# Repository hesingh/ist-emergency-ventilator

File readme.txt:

ABOUT:
The enclosed files belong to the eVent IST ventilator project, inspired by the MIT E-Vent project (see https://e-vent.mit.edu/). We developed the ventilator system using technical documentation of MIT, infrastructure of IST AUSTIRA and consulting of three medical practitioners. We developed and built with great care and focus on stability and safety, still the device is not certified and not built according to all applicable regulations. Please note that this is work in progress and has never been tested on a human. The goal of the eVent IST ventilator project is to provide a simple and fast to replicate system for emergency response, and was created in reaction to the COVID-19 crisis early 2020. Furthermore, its intention is not to replace common ventilator systems, but to bridge a situation where not enough conventional machines are available.

ATTRIBUTION:
Please notice that the eVent IST ventilator was developed using the information shared by the Massachusetts Institute of Technology (MIT). You can find information on the original MIT E-Vent project under https://e-vent.mit.edu/. All Terms of Use, found here: https://e-vent.mit.edu/terms-and-conditions/, concerning the original MIT content do apply.
3rd party libraries used: Encoder by Paul Stoffregen (https://github.com/PaulStoffregen/Encoder), LiquidCrystal (https://github.com/arduino-libraries/LiquidCrystal).

FOLDERS:

	Folder name	Description							Origin
	------------------------------------------------------------------------------------------------
	Electronics	contains files for the electronic parts of the ventilator	mostly MIT E-Vent
	License		contains relevant license files					https://opensource.org
	Mechanical	contains files for the mechanical parts of the ventilator	mostly MIT E-Vent
	Pictures	contains pictures of the machine				IST AUSTRIA
	Software	contains files for the software of the ventilator		IST AUSTRIA

COPYRIGHT AND LICENSE: 
Selected Content may be downloaded by you pursuant to these Terms of Use. All copyright in and to the original MIT E-Vent Design Specifications belong to MIT. MIT is making the Design Specifications freely available to you to use, subject to these Terms of Use and your agreement to give full attribution to MIT should you reproduce, display, disseminate, or distribute the Design Specifications. All copyright in and to content going beyond the MIT E-Vent Design Specifications, and especially the software, belong to IST AUSTRIA. If and to the extent you provide any feedback, suggestions, recommendations, analysis or other information or data to IST in connection with your use of the Content (“Feedback”), you hereby permit IST to use, reproduce, disclose, distribute, modify, and prepare derivative works of such Feedback for any purpose whatsoever in perpetuity. Any downloadable software is subject to the MIT Open Source license, found here: https://opensource.org/licenses/MIT.
3rd party libraries included: Encoder: (MIT License), LiquidCrystal: LGPL License v3 (https://opensource.org/licenses/LGPL-3.0).

DISCLAIMER OF WARRANTIES
YOU ACKNOWLEDGE THAT THE CONTENT IS IN RESEARCH PHASE AND ALL OUTCOMES FROM USE OF THE CONTENT ARE NOT KNOWN. YOUR USE OF THE CONTENT, INCLUDING THE DESIGN SPECIFICATIONS AND THE SOFTWARE, IS AT YOUR OWN RISK. THE CONTENT, INCLUDING THE DESIGN SPECIFICATIONS AND THE SOFTWARE, ARE PROVIDED ON AN “AS IS” AND “AS AVAILABLE” BASIS. 
IST AUSTRIA, ON BEHALF OF ITSELF AND ITS COLLABORATORS, MAKES NO REPRESENTATIONS, WARRANTIES OR COVENANTS, WHETHER STATUTORY, EXPRESS, IMPLIED, BY COURSE OF COMMUNICATION OR DEALING, OR OTHERWISE WITH RESPECT TO THE CONTENT, INCLUDING THE DESIGN SPECIFICATIONS AND THE SOFTWARE, AND ANY RESULTING DEVICE.  IST AUSTRIA, ON BEHALF OF ITSELF AND ITS COLLABORATORS, SPECIFICALLY DISCLAIMS ANY WARRANTY WITH REGARD TO FITNESS FOR ANY PARTICULAR PURPOSE, MERCHANTABILITY OR NON-INFRINGEMENT.
WITHOUT LIMITING THE GENERALITY OF THE FOREGOING, IST AUSTRIA, ON BEHALF OF ITSELF AND ITS COLLABORATORS, MAKES NO WARRANTY OF ANY KIND THAT THE CONTENT, INCLUDING THE DESIGN SPECIFICATIONS AND THE SOFTWARE, AND ANY RESULTING DEVICE OR THE RESULTS OF THE USE OF SUCH DEVICE WILL MEET YOUR OR ANY THIRD PARTY’S REQUIREMENTS, OR ACHIEVE ANY INTENDED RESULT OR THAT THE USE OF THE DESIGN SPECIFICATIONS AND THE SOFTWARE TO MAKE A DEVICE WILL COMPLY WITH INTERNATIONAL, FEDERAL, STATE OR MUNICIPAL LAWS AND REGULATIONS REGARDING MEDICAL DEVICES OR MEDICAL USES.  YOU EXPRESSLY ACKNOWLEDGE AND AGREE THAT IST AUSTRIA, ON BEHALF OF ITSELF AND ITS COLLABORATORS, IS NOT RESPONSIBLE FOR ANY HEALTH PROBLEMS, INJURIES OR DEATH THAT MAY RESULT FROM YOUR OR ANY THIRD PARTY’S USE OF ANY DEVICE RESULTING FROM YOUR USE OF THE CONTENT, INCLUDING THE DESIGN SPECIFICATIONS AND THE SOFTWARE.  IT IS UNDERSTOOD THAT IST AUSTRIA DOES NOT PROVIDE MEDICAL OR OTHER HEALTH-RELATED ADVICE.     
IST AUSTRIA, ON BEHALF OF ITSELF AND ITS COLLABORATORS, DISCLAIMS ANY RESPONSIBILITY FOR OR ASSURANCES REGARDING THE QUALITY, FUNCTIONALITY, OR SAFETY OF ANY DEVICE RESULTING FROM YOUR USE OF THE CONTENT, INCLUDING THE DESIGN SPECIFICATIONS AND THE SOFTWARE, OR ANY DEFECT, ERRORS OR MALFUNCTION IN CONNECTION THEREWITH.  FURTHER, IST AUSTRIA, ON BEHALF OF ITSELF AND ITS COLLABORATORS, DISCLAIMS ANY RESPONSIBILITY FOR OR ASSURANCES REGARDING ANY COMMENTS, FEEDBACK, INFORMATION OR OTHER KNOW-HOW PROVIDED BY ANY USER. YOU RELY ON USER COMMENTS, FEEDBACK, INFORMATION AND/OR KNOW-HOW SOLELY AT YOUR OWN RISK. 
YOU UNDERSTAND AND ACKNOWLEDGE THAT: YOU ARE A LEARNED INDIVIDUAL THAT HAS HAD THE OPPORTUNITY TO OBTAIN ANY AND ALL INFORMATION RELEVANT TO THE USE OF ANY DEVICE RESULTING FROM YOUR USE OF THE CONTENT, INCLUDING THE DESIGN SPECIFICATIONS AND THE SOFTWARE; YOU HAVE NO OBLIGATION TO USE THE CONTENT, THE DESIGN SPECIFICATIONS AND THE SOFTWARE OR ANY DEVICE RESULTING THEREFROM AND YOU DO SO IN YOUR SOLE DISCRETION; YOU ARE RESPONSIBLE FOR DETERMINING THE DEGREE OF MONITORING OR OVERSIGHT THAT IS APPROPRIATE IN CONNECTION WITH PATIENT CARE AND THE USE OF ANY DEVICE RESULTING FROM YOUR USE OF THE CONTENT, INCLUDING THE DESIGN SPECIFICATIONS AND THE SOFTWARE; YOU HAVE ACCEPTED ALL RESPONSIBILITY AND IST AUSTRIA, ON BEHALF OF ITSELF AND ITS COLLABORATORS, RETAINS NO RESPONSIBILITY FOR YOUR USE OF ANY RESULTING DEVICE; AND YOU WILL COMPLY WITH ALL LAWS AND GOVERNMENTAL RULES, REGULATIONS AND GUIDELINES, INCLUDING ANY SAFETY PRECAUTIONS, THAT ARE APPLICABLE TO THE DEVICE OR THE USE THEREOF.
IST AUSTRIA does not guarantee or warrant that files available for downloading from the Internet or the Site will be free of viruses or other destructive code. NEITHER IST AUSTRIA NOR ANY PERSON ASSOCIATED WITH IST AUSTRIA MAKES ANY WARRANTY OR REPRESENTATION WITH RESPECT TO THE SECURITY, RELIABILITY, QUALITY, OR AVAILABILITY OF THE SITE AND THE CONTENT. IST AUSTRIA WILL NOT BE LIABLE FOR ANY LOSS OR DAMAGE CAUSED BY A DISTRIBUTED DENIAL-OF-SERVICE ATTACK, VIRUSES OR OTHER TECHNOLOGICALLY HARMFUL MATERIAL THAT MAY INFECT YOUR COMPUTER EQUIPMENT, COMPUTER PROGRAMS, DATA OR OTHER PROPRIETARY MATERIAL DUE TO YOUR USE OF THE CONTENT, YOUR DOWNLOADING OF ANY AVAILABLE CONTENT, OR YOUR USE OF ANY WEBSITE LINKED TO THE CONTENT.  

LIMITATION OF LIABILITY
TO THE FULLEST EXTENT ALLOWABLE BY LAW, IN NO EVENT WILL IST AUSTRIA, ITS TRUSTEES, DIRECTORS, OFFICERS, FACULTY, STUDENTS, EMPLOYEES, AGENTS, AFFILIATES, VOLUNTEERS, AND COLLABORATORS AND THEIR RESPECTIVE SUCCESSORS, HEIRS AND ASSIGNS BE LIABLE OR RESPONSIBLE FOR, OR INDEMNIFY YOU OR ANY THIRD PARTY FOR, DIRECT, INDIRECT, SPECIAL, INCIDENTAL, CONSEQUENTIAL, PUNITIVE OR EXEMPLARY DAMAGES OF ANY KIND, UNDER ANY LEGAL THEORY, ARISING OUT OF OR IN CONNECTION WITH YOUR USE, OR INABILITY TO USE, THE CONTENT (INCLUDING THE DESIGN SPECIFICATIONS AND THE SOFTWARE), ANY WEBSITES LINKED TO THE SITE OR CONTENT OR ANY INFORMATION OBTAINED THROUGH THE CONTENT OR SUCH THIRD PARTY WEBSITES (INCLUDING BUT NOT LIMITED TO COMMENTS, FEEDBACK, INFORMATION AND KNOW-HOW FROM OTHER USERS); ANY USE OF A RESULTING DEVICE; ANY ERROR, FAILURE OR DEFECT OF SUCH DEVICE; OR ANY HARM OR INJURY CAUSED BY SUCH DEVICE.

INDEMNIFICATION
To the fullest extent permitted by law, you shall indemnify IST AUSTRIA and all of its trustees, directors, officers, faculty, students, employees, agents, affiliates, volunteers, and collaborators and their respective successors, heirs and assigns (collectively, the “Indemnified Parties”) from and against any and all losses and liabilities, including, without limitation, reasonable attorneys’ fees incurred by the Indemnified Parties in connection with any claim arising from or related to your breach of these Terms of Use, your use of, or inability to use, the Content and your use of any information obtained through use of the Site and Content. You shall cooperate as fully as reasonably required in the defense of any such claim.

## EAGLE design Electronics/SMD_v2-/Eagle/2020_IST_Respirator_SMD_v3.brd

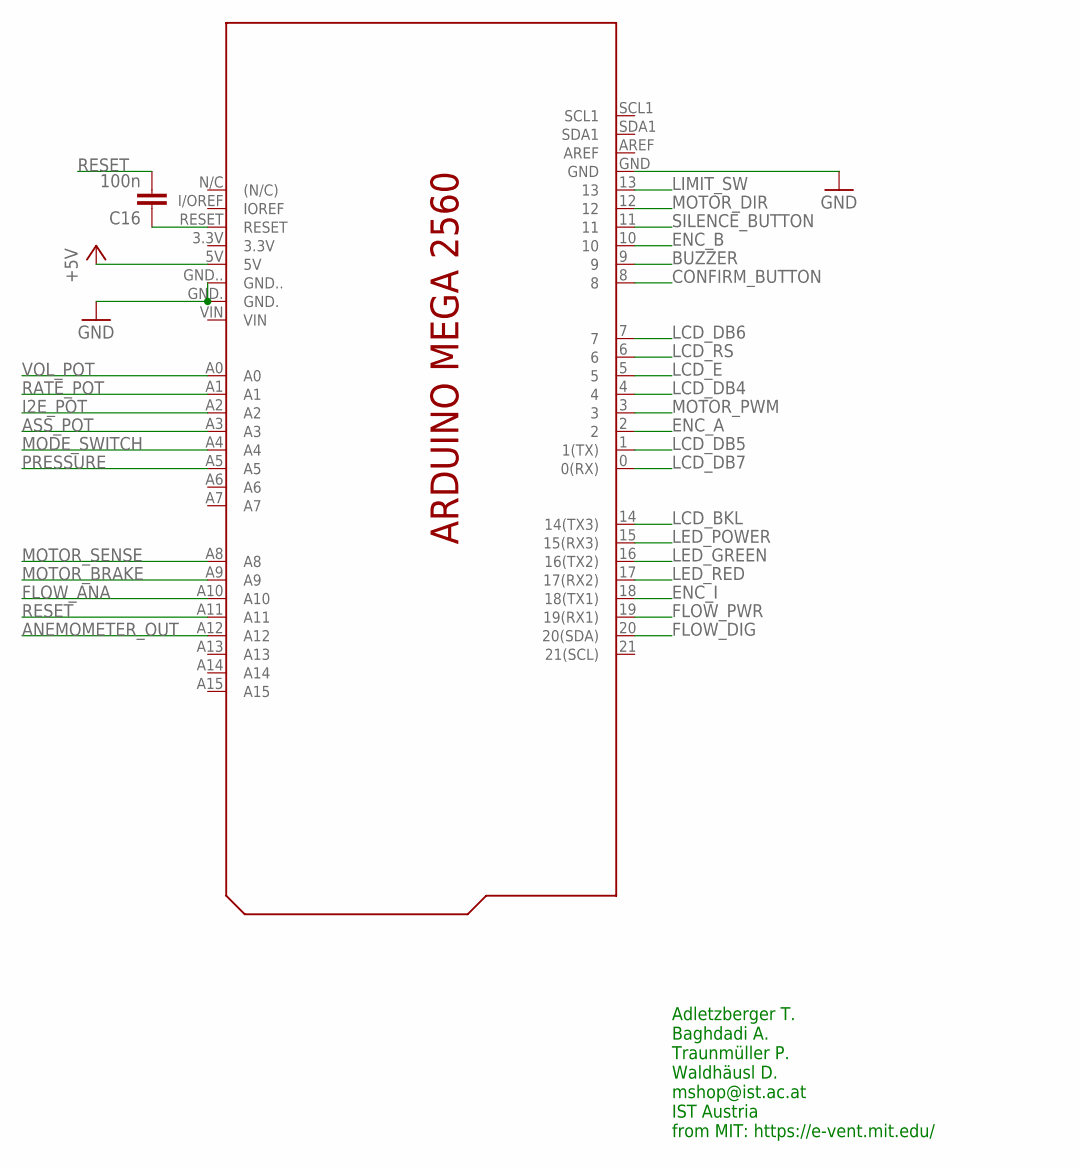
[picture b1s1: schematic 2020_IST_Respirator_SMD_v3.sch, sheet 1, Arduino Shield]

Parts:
C16: 100n; C0805
PCB1: ARDUINO_MEGA2560_NOTALLPINS

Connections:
+5V: PCB1.5V; also elsewhere on the board
ANEMOMETER_OUT: PCB1.A12
ASS_POT: PCB1.A3; also elsewhere on the board
BUZZER: PCB1.9; also elsewhere on the board
CONFIRM_BUTTON: PCB1.8; also elsewhere on the board
ENC_A: PCB1.2; also elsewhere on the board
ENC_B: PCB1.10; also elsewhere on the board
ENC_I: PCB1.18 (18(TX1)); also elsewhere on the board
FLOW_ANA: PCB1.A10; also elsewhere on the board
FLOW_DIG: PCB1.20 (20(SDA)); also elsewhere on the board
FLOW_PWR: PCB1.19 (19(RX1)); also elsewhere on the board
GND: PCB1.GND, PCB1.GND., PCB1.GND..; also elsewhere on the board
I2E_POT: PCB1.A2; also elsewhere on the board
LCD_BKL: PCB1.14 (14(TX3)); also elsewhere on the board
LCD_DB4: PCB1.4; also elsewhere on the board
LCD_DB5: PCB1.1 (1(TX)); also elsewhere on the board
LCD_DB6: PCB1.7; also elsewhere on the board
LCD_DB7: PCB1.0 (0(RX)); also elsewhere on the board
LCD_E: PCB1.5; also elsewhere on the board
LCD_RS: PCB1.6; also elsewhere on the board
LED_GREEN: PCB1.16 (16(TX2)); also elsewhere on the board
LED_POWER: PCB1.15 (15(RX3)); also elsewhere on the board
LED_RED: PCB1.17 (17(RX2)); also elsewhere on the board
LIMIT_SW: PCB1.13; also elsewhere on the board
MODE_SWITCH: PCB1.A4; also elsewhere on the board
MOTOR_BRAKE: PCB1.A9
MOTOR_DIR: PCB1.12; also elsewhere on the board
MOTOR_PWM: PCB1.3; also elsewhere on the board
MOTOR_SENSE: PCB1.A8; also elsewhere on the board
unnamed: C16.1, PCB1.RESET
PRESSURE: PCB1.A5; also elsewhere on the board
RATE_POT: PCB1.A1; also elsewhere on the board
RESET: C16.2, PCB1.A11
SILENCE_BUTTON: PCB1.11; also elsewhere on the board
VOL_POT: PCB1.A0; also elsewhere on the board

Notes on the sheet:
Adletzberger T. Baghdadi A. Traunmüller P. Waldhäusl D. mshop@ist.ac.at IST Austria from MIT: https://e-vent.mit.edu/

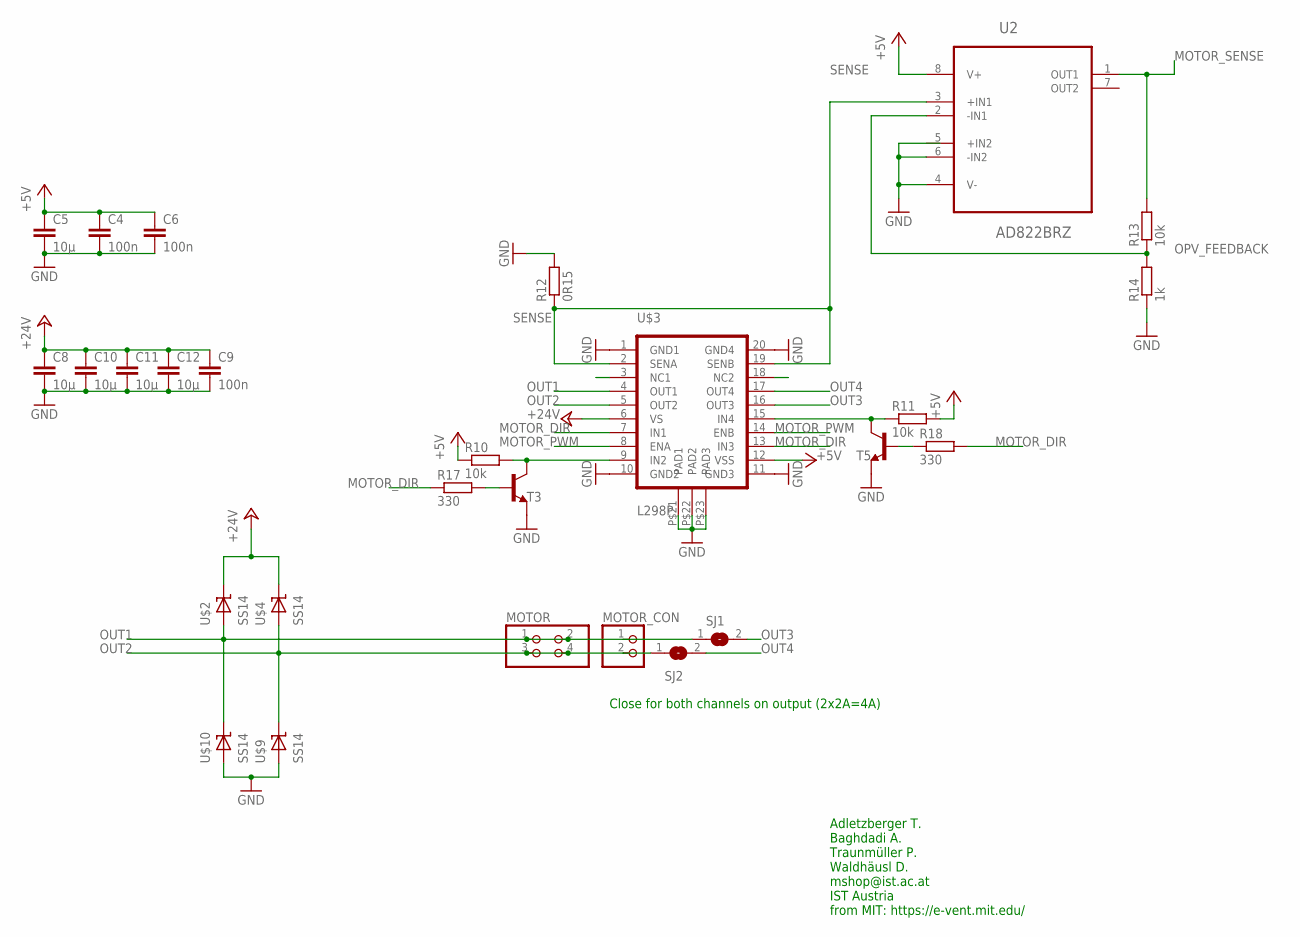
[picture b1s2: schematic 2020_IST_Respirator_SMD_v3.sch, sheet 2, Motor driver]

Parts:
C4, C6, C9: 100n; C0805
C5, C8, C10, C11, C12: 10µ; C1210
MOTOR: PINHD-2X2; 2X02
MOTOR_CON: PINHD-1X2_3.93MM; 1X02_3.96MM
R10, R11, R13: 10k; R0805
R12: 0R15; R1206
R14: 1k; R0805
R17, R18: 330; R0805
SJ1, SJ2: SJ
T3, T5: MMBT3904LT1-NPN-SOT23-BEC; SOT23-BEC
U2: AD822BRZ; SOIC127P600X175-8N
U$2, U$4, U$9, U$10: SS14; SMA
U$3: L298P; POWER-SO20

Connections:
+5V: C4.1, C5.1, C6.1, R10.1, R11.2, U2.8 (V+), U$3.P$12 (VSS); also elsewhere on the board
+24V: C8.1, C9.1, C10.1, C11.1, C12.1, U$2.P$1 (K), U$3.P$6 (VS), U$4.P$1 (K); also elsewhere on the board
DRIVER_IN2: R10.2, T3.C, U$3.P$9 (IN2)
DRIVER_INV4: R11.1, T5.C, U$3.P$15 (IN4)
GND: C4.2, C5.2, C6.2, C8.2, C9.2, C10.2, C11.2, C12.2, R12.2, R14.1, T3.E, T5.E, U2.4 (V-), U2.6 (-IN2), U$3.P$1 (GND1), U$3.P$10 (GND2), U$3.P$11 (GND3), U$3.P$20 (GND4), U$3.P$21 (PAD1), U$3.P$22 (PAD2), U$3.P$23 (PAD3), U$9.P$2 (A), U$10.P$2 (A); also elsewhere on the board
MOTOR_DIR: R17.1, R18.2, U$3.P$7 (IN1), U$3.P$13 (IN3); also elsewhere on the board
MOTOR_PWM: U$3.P$8 (ENA), U$3.P$14 (ENB); also elsewhere on the board
MOTOR_SENSE: R13.2, U2.1 (OUT1); also elsewhere on the board
unnamed: R17.2, T3.B
unnamed: R18.1, T5.B
OPV_FEEDBACK: R13.1, R14.2, U2.2 (-IN1)
OUT1: MOTOR.1, MOTOR.2, MOTOR_CON.1, SJ1.1, U$2.P$2 (A), U$3.P$4 (OUT1), U$10.P$1 (K)
OUT2: MOTOR.3, MOTOR.4, MOTOR_CON.2, SJ2.1, U$3.P$5 (OUT2), U$4.P$2 (A), U$9.P$1 (K)
OUT3: SJ1.2, U$3.P$16 (OUT3)
OUT4: SJ2.2, U$3.P$17 (OUT4)
SENSE: R12.1, U2.3 (+IN1), U$3.P$2 (SENA), U$3.P$19 (SENB)

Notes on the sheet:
Close for both channels on output (2x2A=4A)
Adletzberger T. Baghdadi A. Traunmüller P. Waldhäusl D. mshop@ist.ac.at IST Austria from MIT: https://e-vent.mit.edu/

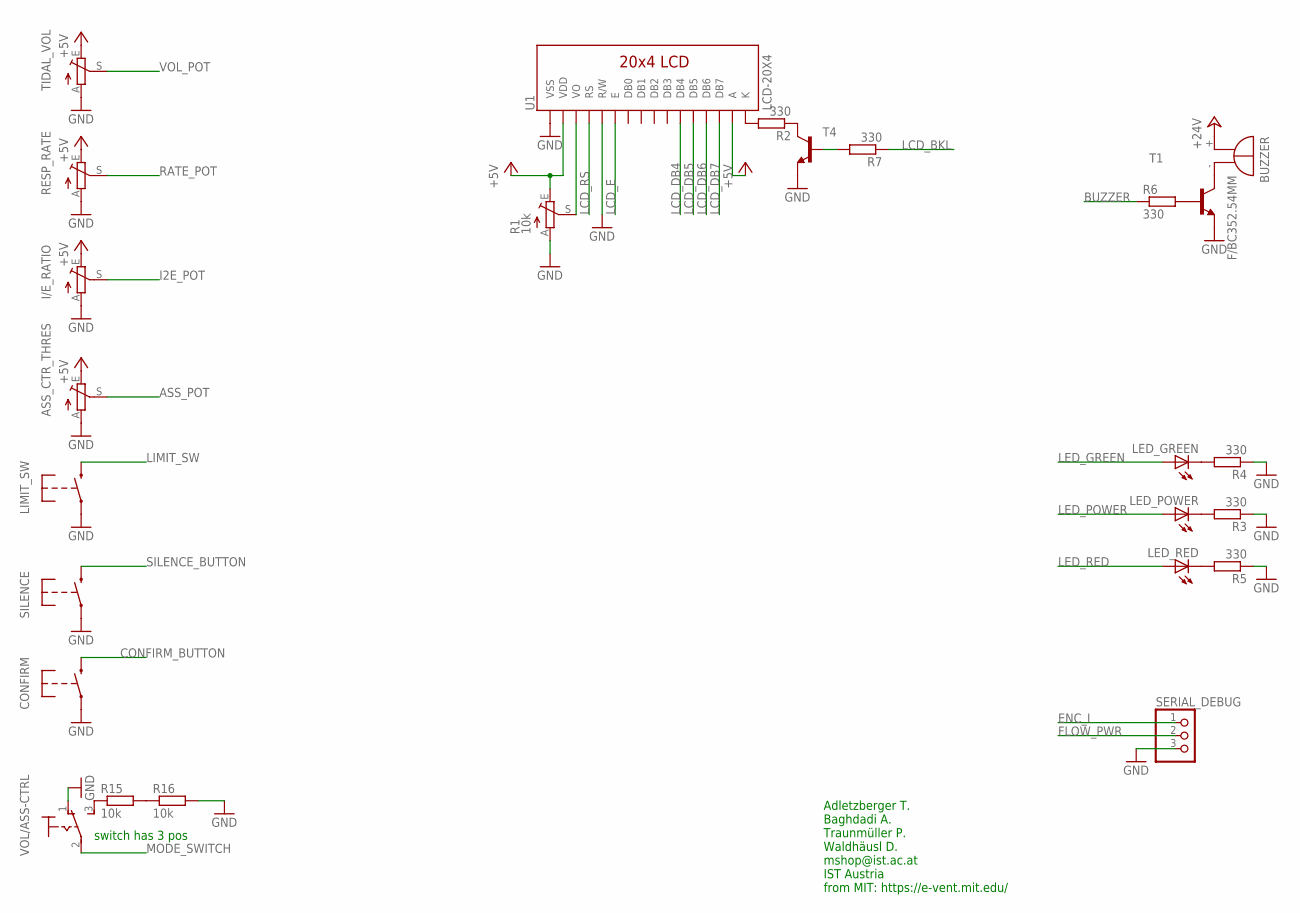
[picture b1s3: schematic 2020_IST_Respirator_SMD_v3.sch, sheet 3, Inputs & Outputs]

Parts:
ASS_CTR_THRES: TRIM_EU-ROUND; S64W_ROUND-PADS
BUZZER: F/BC352.54MM; F/BC35_2.54MM
CONFIRM: SWITCH-MOMENTARY-22.54; TACTILE-2.54MM
I/E_RATIO: TRIM_EU-ROUND; S64W_ROUND-PADS
LED_GREEN: LED5MM
LED_POWER: LED5MM
LED_RED: LED5MM
LIMIT_SW: SWITCH-MOMENTARY-22.54; TACTILE-2.54MM
R1: 10k; S64W
R2, R3, R4, R5, R6, R7: 330; R0805
R15, R16: 10k; R0805
RESP_RATE: TRIM_EU-ROUND; S64W_ROUND-PADS
SERIAL_DEBUG: PINHD-1X3; 1X03
SILENCE: SWITCH-MOMENTARY-22.54; TACTILE-2.54MM
T1, T4: MMBT3904LT1-NPN-SOT23-BEC; SOT23-BEC
TIDAL_VOL: TRIM_EU-ROUND; S64W_ROUND-PADS
U1: LCD-20X4
VOL/ASS-CTRL: 320-9162.54MM-ROUND-PADS; 320-916:2.54MM:ROUND-PADS

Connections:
+5V: ASS_CTR_THRES.E, I/E_RATIO.E, R1.E, RESP_RATE.E, TIDAL_VOL.E, U1.2 (VDD), U1.15 (A); also elsewhere on the board
+24V: BUZZER.+; also elsewhere on the board
ASS_POT: ASS_CTR_THRES.S; also elsewhere on the board
BUZZER: R6.1; also elsewhere on the board
CONFIRM_BUTTON: CONFIRM.3 (2); also elsewhere on the board
ENC_I: SERIAL_DEBUG.1; also elsewhere on the board
FLOW_PWR: SERIAL_DEBUG.2; also elsewhere on the board
GND: ASS_CTR_THRES.A, CONFIRM.1, I/E_RATIO.A, LIMIT_SW.1, R1.A, R3.1, R4.1, R5.1, R16.2, RESP_RATE.A, SERIAL_DEBUG.3, SILENCE.1, T1.E, T4.E, TIDAL_VOL.A, U1.1 (VSS), U1.5 (R/W), VOL/ASS-CTRL.1 (O); also elsewhere on the board
I2E_POT: I/E_RATIO.S; also elsewhere on the board
LCD_BKL: R7.1; also elsewhere on the board
LCD_DB4: U1.11 (DB4); also elsewhere on the board
LCD_DB5: U1.12 (DB5); also elsewhere on the board
LCD_DB6: U1.13 (DB6); also elsewhere on the board
LCD_DB7: U1.14 (DB7); also elsewhere on the board
LCD_E: U1.6 (E); also elsewhere on the board
LCD_RS: U1.4 (RS); also elsewhere on the board
LED_GREEN: LED_GREEN.A; also elsewhere on the board
LED_POWER: LED_POWER.A; also elsewhere on the board
LED_RED: LED_RED.A; also elsewhere on the board
LIMIT_SW: LIMIT_SW.3 (2); also elsewhere on the board
MODE_SWITCH: VOL/ASS-CTRL.2; also elsewhere on the board
unnamed: BUZZER.-, T1.C
unnamed: R6.2, T1.B
unnamed: R2.1, T4.C
unnamed: R7.2, T4.B
unnamed: R15.1, VOL/ASS-CTRL.3 (S)
unnamed: R15.2, R16.1
unnamed: R2.2, U1.16 (K)
unnamed: R1.S, U1.3 (VO)
unnamed: LED_GREEN.K (C), R4.2
unnamed: LED_POWER.K (C), R3.2
unnamed: LED_RED.K (C), R5.2
RATE_POT: RESP_RATE.S; also elsewhere on the board
SILENCE_BUTTON: SILENCE.3 (2); also elsewhere on the board
VOL_POT: TIDAL_VOL.S; also elsewhere on the board

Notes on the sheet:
Adletzberger T. Baghdadi A. Traunmüller P. Waldhäusl D. mshop@ist.ac.at IST Austria from MIT: https://e-vent.mit.edu/
switch has 3 pos

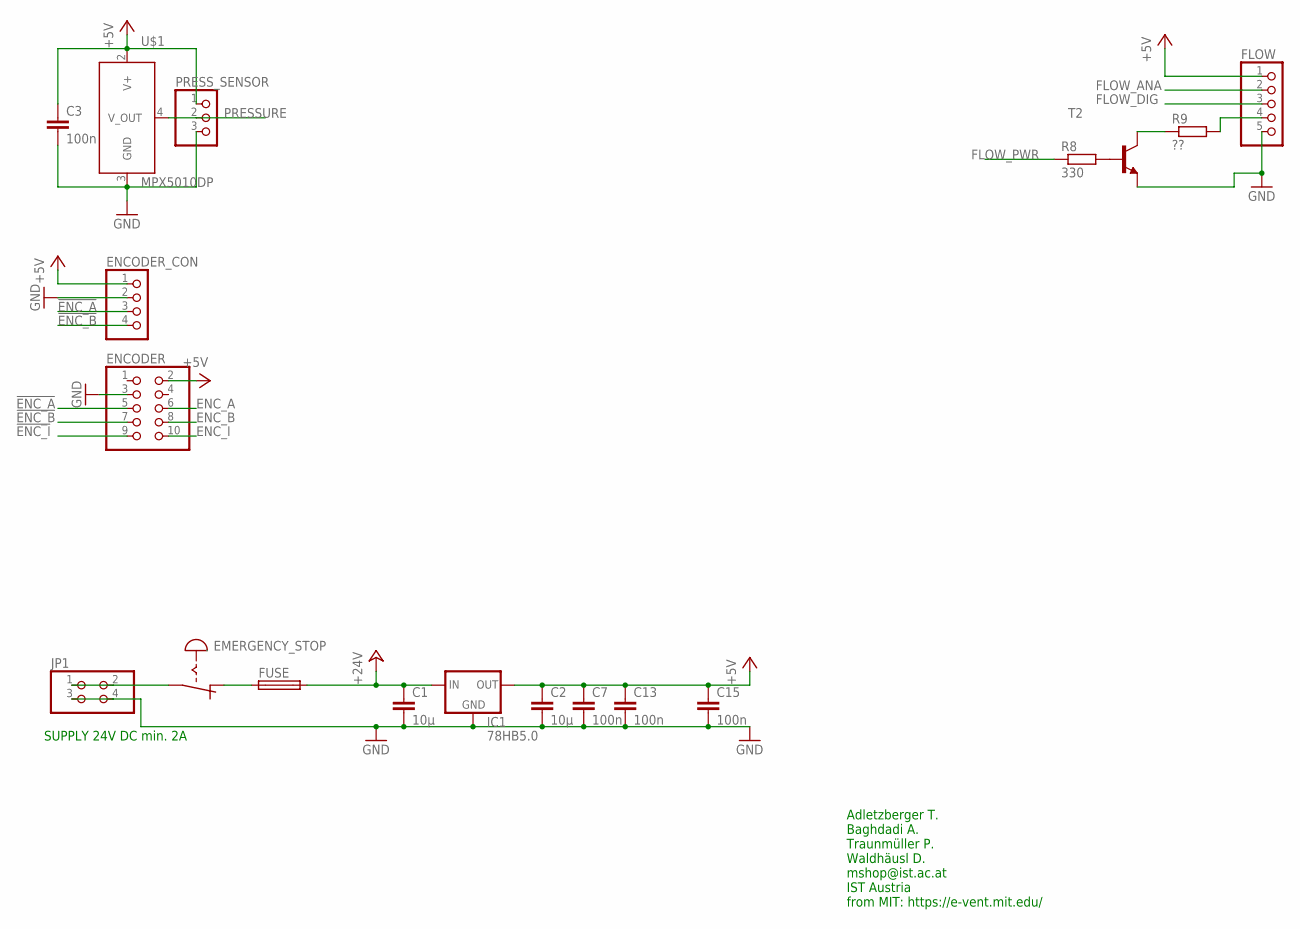
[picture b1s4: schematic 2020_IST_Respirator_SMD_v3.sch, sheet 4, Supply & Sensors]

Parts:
C1, C2: 10µ; C1210
C3, C7, C13, C15: 100n; C0805
EMERGENCY_STOP: EMERGENCY_STOP; 320-916:2.54MM:ROUND-PAD_2PINS
ENCODER: PINHD-2X5; 2X05
ENCODER_CON: PINHD-1X42MM; 1_04X2MM
FLOW: PINHD-1X5; 1X05
FUSE: SH22,5
IC1: 78HB5.0; R-78HB
JP1: PINHD-2X2; 2X02
PRESS_SENSOR: PINHD-1X3; 1X03
R8: 330; R0805
R9: ??; R0805
T2: MMBT3904LT1-NPN-SOT23-BEC; SOT23-BEC
U$1: MPX5010DP; MPX5010DP_SOP482

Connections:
!ENC_A: ENCODER.5, ENCODER_CON.3
!ENC_B: ENCODER.7, ENCODER_CON.4
!ENC_I: ENCODER.9
+5V: C2.1, C3.1, C7.1, C13.1, C15.1, ENCODER.2, ENCODER_CON.1, FLOW.1, IC1.OUT, PRESS_SENSOR.1, U$1.2 (V+); also elsewhere on the board
+24V: C1.1, FUSE.2, IC1.IN; also elsewhere on the board
ENC_A: ENCODER.6; also elsewhere on the board
ENC_B: ENCODER.8; also elsewhere on the board
ENC_I: ENCODER.10; also elsewhere on the board
FLOW_ANA: FLOW.2; also elsewhere on the board
FLOW_DIG: FLOW.3; also elsewhere on the board
FLOW_PWR: R8.1; also elsewhere on the board
GND: C1.2, C2.2, C3.2, C7.2, C13.2, C15.2, ENCODER.3, ENCODER_CON.2, FLOW.5, IC1.GND, JP1.3, JP1.4, PRESS_SENSOR.3, T2.E, U$1.3 (GND); also elsewhere on the board
unnamed: R8.2, T2.B
unnamed: R9.1, T2.C
unnamed: FLOW.4, R9.2
unnamed: EMERGENCY_STOP.2, JP1.1, JP1.2
unnamed: EMERGENCY_STOP.1, FUSE.1
PRESSURE: PRESS_SENSOR.2, U$1.4 (V_OUT); also elsewhere on the board

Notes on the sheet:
SUPPLY 24V DC min. 2A
Adletzberger T. Baghdadi A. Traunmüller P. Waldhäusl D. mshop@ist.ac.at IST Austria from MIT: https://e-vent.mit.edu/

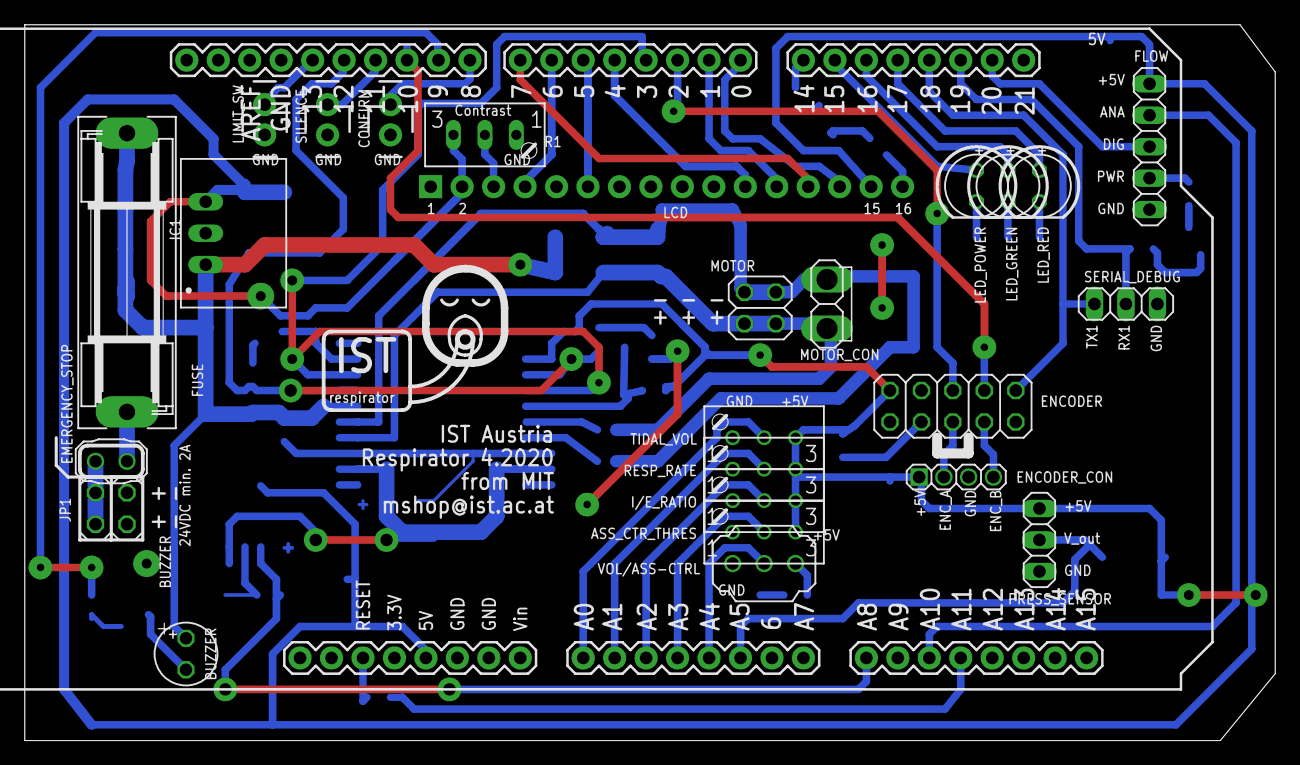
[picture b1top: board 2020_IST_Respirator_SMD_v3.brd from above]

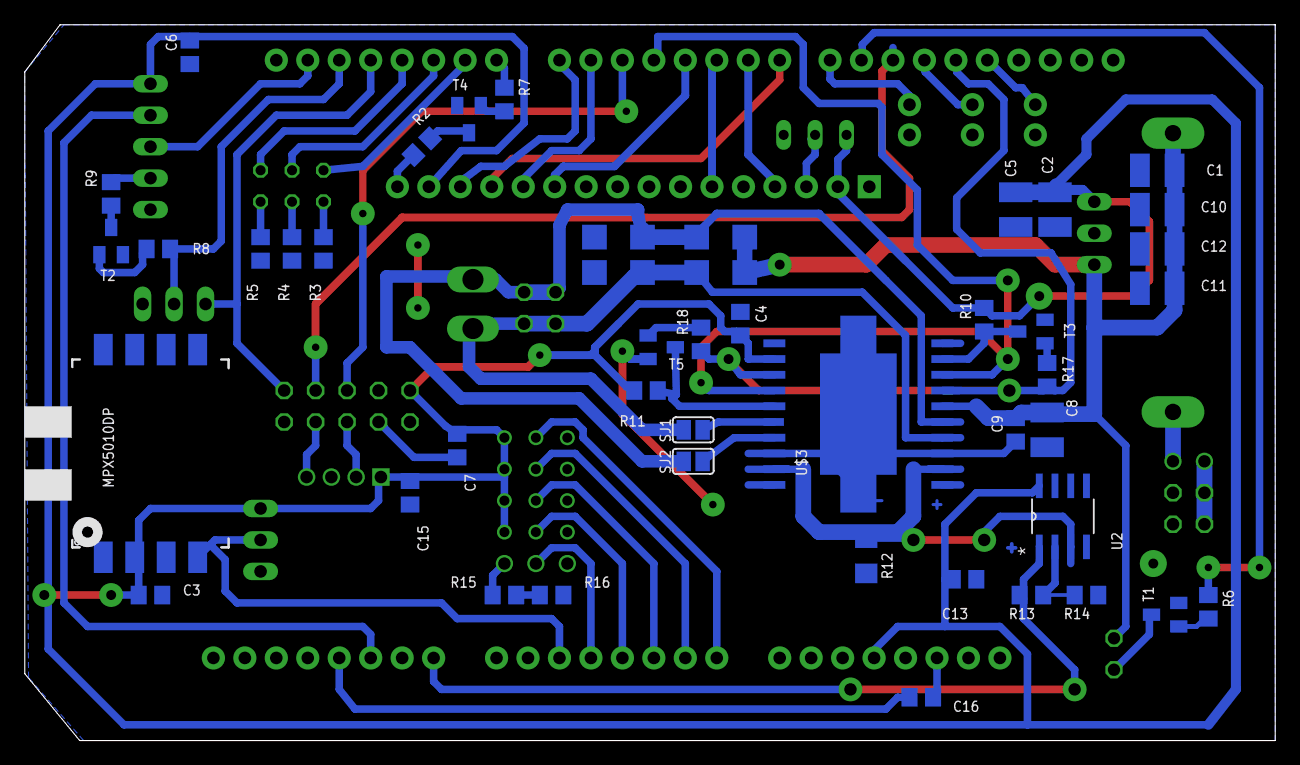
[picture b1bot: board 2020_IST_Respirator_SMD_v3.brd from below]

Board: 2 copper layers, 101.0 x 57.8 mm, 72 parts (46 on the bottom side), 62 nets.

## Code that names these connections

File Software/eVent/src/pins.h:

//analog sensors
#define PRESSURE A5       //(922-7409), analog 0.2-4.7V, 0-1019.78mmH2O

#define LIMIT_SWITCH   13     //limit switch for homing

//control potentiometers, single turn 10k, analog 0-5V (789-9438)
#define VOL_POT A0            //sets volume setpoint in ml
#define RATE_POT A1           //sets breaths per minute 5-40 BPM
#define I2E_POT A2            //sets inspiration/expiration time ratio 1:1 - 1:4
#define PRS_POT A3            //sets max pressure

//switches and buttons
#define MODE_SWITCH A4         //selects volume or assist control
#define SILENCE_BUTTON 11         // momentary button to mute alarms
#define CONFIRM_BUTTON  8          // momentary buttton to confirm potentiometer changes

//OUTPUTS
#define BUZZER      9             //piezo buzzer (724-3178) PWM

//Display
#define LCD_RS      6
#define LCD_ENABLE  5
#define LCD_D4      4
#define LCD_D5      1
#define LCD_D6      7
#define LCD_D7      0
#define LCD_BACKLIGHT 14


//Encoder
#define ENC_A   2
#define ENC_B   10
#define ENC_I   18

//Leds
#define LED_POWER 15
#define LED_GREEN 16
#define LED_RED 17

#define RESET_PIN A11

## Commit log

2020-04-23 Add LICENSE
2020-04-24 Inhale time calculation simplified + user manual V0.1
2020-04-24 Adding the SMD version of circuit
2020-04-24 Adding the SMD version of circuit & updating user manual
2020-04-24 Updated SMD v3, added gerbers and board pdfs
2020-04-26 Remove motor code to use software for alarms and monitoring using only pressure sensor
2020-04-26 Remove more motor code and fix lint error

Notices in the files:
parts and their libraries:
SparkFun: Licensing: CC v3.0 Share-Alike You are welcome to use this library for commercial purposes.
